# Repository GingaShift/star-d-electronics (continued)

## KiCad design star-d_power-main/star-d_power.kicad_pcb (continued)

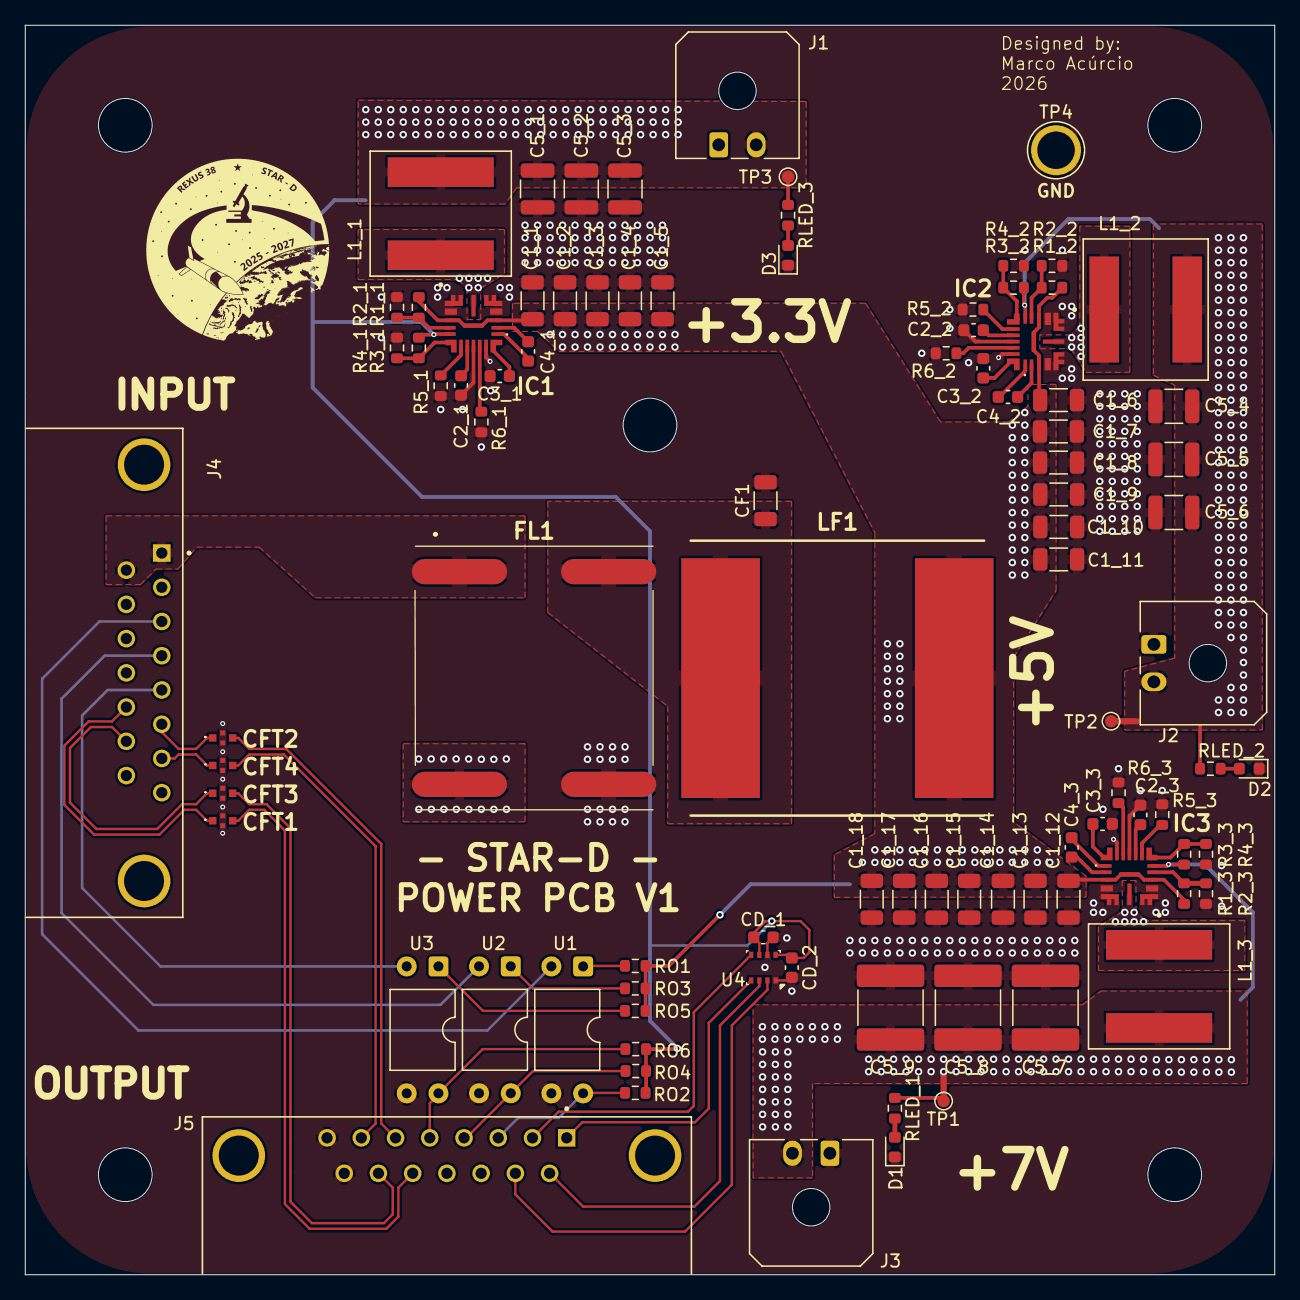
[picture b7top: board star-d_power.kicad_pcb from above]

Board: 4 copper layers, 100.0 x 100.0 mm, 94 parts (0 on the bottom side), 59 nets.

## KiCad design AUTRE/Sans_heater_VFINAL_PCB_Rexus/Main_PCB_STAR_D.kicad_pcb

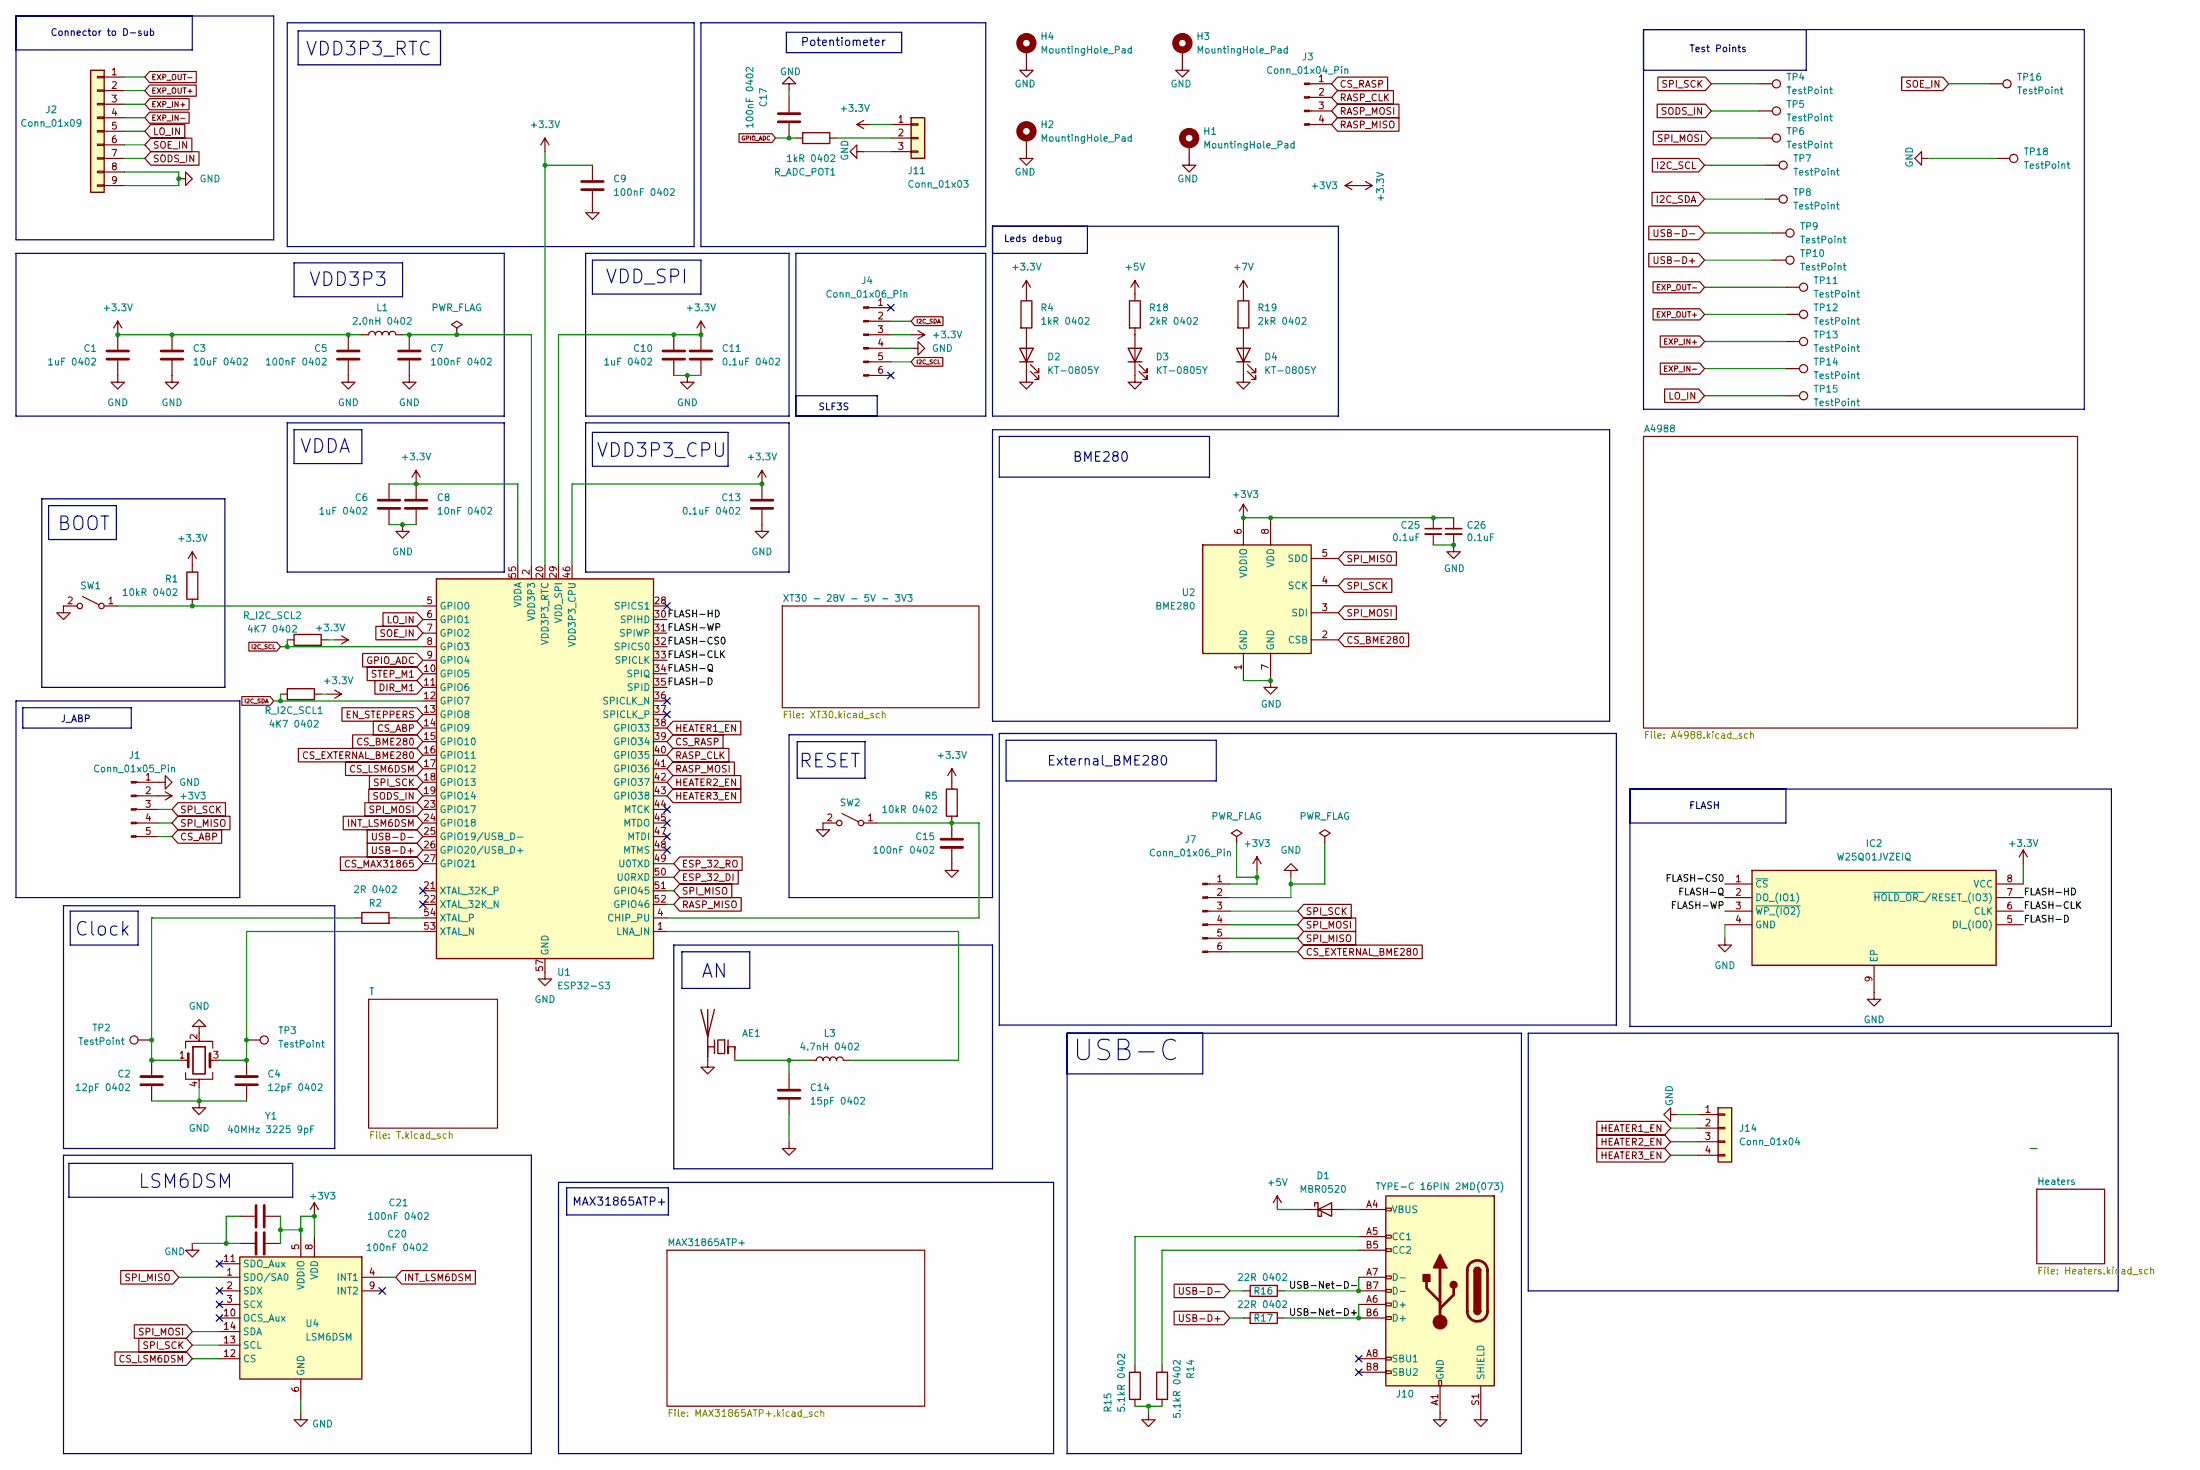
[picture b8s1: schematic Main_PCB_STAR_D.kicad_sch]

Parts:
AE1: Antenna_Chip; U.FL_Molex_MCRF_73412-0110_Vertical
C1, C6, C10: 1uF 0402; C_0402_1005Metric
C2, C4: 12pF 0402; C_0402_1005Metric
C3: 10uF 0402; C_0402_1005Metric
C5, C7, C9, C15, C17, C20, C21: 100nF 0402; C_0402_1005Metric
C8: 10nF 0402; C_0402_1005Metric
C11, C13: 0.1uF 0402; C_0402_1005Metric
C14: 15pF 0402; C_0402_1005Metric
C25, C26: 0.1uF; C_0402_1005Metric
D1: MBR0520; D_SOD-123
D2, D3, D4: KT-0805Y; LED_0805_2012Metric
H1, H2, H3, H4: MountingHole_Pad; MountingHole_4.3mm_M4_DIN965_Pad
IC2: W25Q01JVZEIQ; WSON-8-1EP_6x5mm_P1.27mm_EP3.4x4.3mm; Manufacturer_Part_Number W25Q01JVZEIQ; Mouser Part Number 454-W25Q01JVZEIQ
J1: Conn_01x05_Pin; JST_EH_S5B-EH_1x05_P2.50mm_Horizontal
J2: Conn_01x09; JST_GH_BM09B-GHS-TBT_1x09-1MP_P1.25mm_Vertical
J3: Conn_01x04_Pin; JST_EH_S4B-EH_1x04_P2.50mm_Horizontal
J4, J7: Conn_01x06_Pin; JST_EH_S6B-EH_1x06_P2.50mm_Horizontal
J10: TYPE-C 16PIN 2MD(073); USB_C_Receptacle_GCT_USB4105-xx-A_16P_TopMnt_Horizontal
J11: Conn_01x03; JST_EH_S3B-EH_1x03_P2.50mm_Horizontal
J14: Conn_01x04; JST_PH_S4B-PH-K_1x04_P2.00mm_Horizontal
L1: 2.0nH 0402; L_0402_1005Metric
L3: 4.7nH 0402; L_0402_1005Metric
R1, R5: 10kR 0402; R_0402_1005Metric
R2: 2R 0402; R_0402_1005Metric
R4: 1kR 0402; R_0402_1005Metric
R14, R15: 5.1kR 0402; R_0402_1005Metric
R16, R17: 22R 0402; R_0402_1005Metric
R18, R19: 2kR 0402; R_0402_1005Metric
R_ADC_POT1: 1kR 0402; R_0402_1005Metric
R_I2C_SCL1, R_I2C_SCL2: 4K7 0402; R_0402_1005Metric
SW1, SW2: SW_SPST; SW_Tactile_SPST_NO_Straight_CK_PTS636Sx25SMTRLFS
TP2, TP3, TP4, TP5, TP6, TP7, TP8, TP9, TP10, TP11, TP12, TP13, TP14, TP15, TP16, TP18: TestPoint; TestPoint_Pad_1.0x1.0mm
U1: ESP32-S3; QFN-56-1EP_7x7mm_P0.4mm_EP4x4mm
U2: BME280; Bosch_LGA-8_2.5x2.5mm_P0.65mm_ClockwisePinNumbering
U4: LSM6DSM; LGA-14_3x2.5mm_P0.5mm_LayoutBorder3x4y
Y1: 40MHz 3225 9pF; Crystal_SMD_3225-4Pin_3.2x2.5mm

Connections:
+3.3V: C1.1, C3.1, C5.2, C6.1, C8.1, C9.1, C10.1, C11.1, C13.1, C20.2, C21.2, C25.1, C26.1, IC2.8 (VCC), J1.2, J4.3, J7.1, J11.1, L1.1, R1.1, R4.1, R5.1, R_I2C_SCL1.2, R_I2C_SCL2.2, U1.20 (VDD3P3_RTC), U1.29 (VDD_SPI), U1.46 (VDD3P3_CPU), U1.55 (VDDA), U1.56 (VDDA), U2.6 (VDDIO), U2.8 (VDD), U4.5 (VDDIO), U4.8 (VDD); also elsewhere on the board
+5V: D1.1 (K), R18.1; also elsewhere on the board
+7V: R19.1; also elsewhere on the board
/FLASH-CLK: IC2.6 (CLK), U1.33 (SPICLK)
/FLASH-CS0: IC2.1 (~CS), U1.32 (SPICS0)
/FLASH-D: IC2.5 (DI_(IO0)), U1.35 (SPID)
/FLASH-HD: IC2.7 (~HOLD_OR_/RESET_(IO3)), U1.30 (SPIHD)
/FLASH-Q: IC2.2 (DO_(IO1)), U1.34 (SPIQ)
/FLASH-WP: IC2.3 (~WP_(IO2)), U1.31 (SPIWP)
/USB-Net-D+: J10.A6 (D+), J10.B6 (D+), R17.1
/USB-Net-D-: J10.A7 (D-), J10.B7 (D-), R16.1
CS_ABP: J1.5, U1.14 (GPIO9)
CS_BME280: U1.15 (GPIO10), U2.2 (CSB)
CS_EXTERNAL_BME280: J7.6, U1.16 (GPIO11)
CS_LSM6DSM: U1.17 (GPIO12), U4.12 (CS)
CS_MAX31865: U1.27 (GPIO21); also elsewhere on the board
CS_RASP: J3.1, U1.39 (GPIO34)
DIR_M1: U1.11 (GPIO6); also elsewhere on the board
EN_STEPPERS: U1.13 (GPIO8)
ESP_32_DI: U1.50 (U0RXD); also elsewhere on the board
ESP_32_RO: U1.49 (U0TXD); also elsewhere on the board
EXP_IN+: J2.3, TP13.1 (1_1); also elsewhere on the board
EXP_IN-: J2.4, TP14.1 (1_1); also elsewhere on the board
EXP_OUT+: J2.2, TP12.1 (1_1); also elsewhere on the board
EXP_OUT-: J2.1, TP11.1 (1_1); also elsewhere on the board
GND: AE1.2 (PCB_Trace), C1.2, C2.2, C3.2, C4.2, C5.1, C6.2, C7.1, C8.2, C9.2, C10.2, C11.2, C13.2, C14.2, C15.2, C17.2, C20.1, C21.1, C25.2, C26.2, D2.1 (K), D3.1 (K), D4.1 (K), H1.1 (1_1), H2.1 (1_1), H3.1 (1_1), H4.1 (1_1), IC2.4 (GND), IC2.9 (EP), J1.1, J2.8, J2.9, J4.4, J7.2, J10.A1 (GND), J10.A12 (GND), J10.B1 (GND), J10.B12 (GND), J10.S1 (SHIELD), J11.3, J14.1, R14.2, R15.2, SW1.2 (B), SW2.2 (B), TP18.1 (1_1), U1.57 (GND), U2.1 (GND), U2.7 (GND), U4.6 (GND), U4.7 (GND), Y1.2, Y1.4; also elsewhere on the board
GPIO_ADC: C17.1, R_ADC_POT1.2, U1.9 (GPIO4)
HEATER1_EN: J14.2, U1.38 (GPIO33)
HEATER2_EN: J14.3, U1.42 (GPIO37)
HEATER3_EN: J14.4, U1.43 (GPIO38)
I2C_SCL: J4.5, R_I2C_SCL2.1, TP7.1 (1_1), U1.8 (GPIO3)
I2C_SDA: J4.2, R_I2C_SCL1.1, TP8.1 (1_1), U1.12 (GPIO7)
INT_LSM6DSM: U1.24 (GPIO18), U4.4 (INT1)
LO_IN: J2.5, TP15.1 (1_1), U1.6 (GPIO1)
unnamed: AE1.1 (FEED), C14.1, L3.2
unnamed: C2.1, R2.1, TP2.1 (1_1), Y1.1
unnamed: C7.2, L1.2, U1.2 (VDD3P3), U1.3 (VDD3P3)
unnamed: D1.2 (A), J10.A4 (VBUS), J10.A9 (VBUS), J10.B4 (VBUS), J10.B9 (VBUS)
unnamed: D2.2 (A), R4.2
unnamed: D3.2 (A), R18.2
unnamed: D4.2 (A), R19.2
unnamed: J10.A5 (CC1), R15.1
unnamed: J10.B5 (CC2), R14.1
unnamed: J11.2, R_ADC_POT1.1
unnamed: R1.2, SW1.1 (A), U1.5 (GPIO0)
unnamed: C15.1, R5.2, SW2.1 (A), U1.4 (CHIP_PU)
unnamed: L3.1, U1.1 (LNA_IN)
unnamed: C4.1, TP3.1 (1_1), U1.53 (XTAL_N), Y1.3
unnamed: R2.2, U1.54 (XTAL_P)
RASP_CLK: J3.2, U1.40 (GPIO35)
RASP_MISO: J3.4, U1.52 (GPIO46)
RASP_MOSI: J3.3, U1.41 (GPIO36)
SODS_IN: J2.7, TP5.1 (1_1), U1.19 (GPIO14)
SOE_IN: J2.6, TP16.1 (1_1), U1.7 (GPIO2)
SPI_MISO: J1.4, J7.5, U1.51 (GPIO45), U2.5 (SDO), U4.1 (SDO/SA0); also elsewhere on the board
SPI_MOSI: J7.4, TP6.1 (1_1), U1.23 (GPIO17), U2.3 (SDI), U4.14 (SDA); also elsewhere on the board
SPI_SCK: J1.3, J7.3, TP4.1 (1_1), U1.18 (GPIO13), U2.4 (SCK), U4.13 (SCL); also elsewhere on the board
STEP_M1: U1.10 (GPIO5); also elsewhere on the board
USB-D+: R17.2, TP10.1 (1_1), U1.26 (GPIO20/USB_D+)
USB-D-: R16.2, TP9.1 (1_1), U1.25 (GPIO19/USB_D-)

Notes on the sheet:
J_ABP
VDD3P3_CPU
External_BME280
Clock
VDD3P3_RTC
BOOT
VDDA
SLF3S
RESET
BME280
FLASH
VDD3P3
Connector to D-sub
MAX31865ATP+
Leds debug
Test Points
LSM6DSM
VDD_SPI
Potentiometer
USB-C

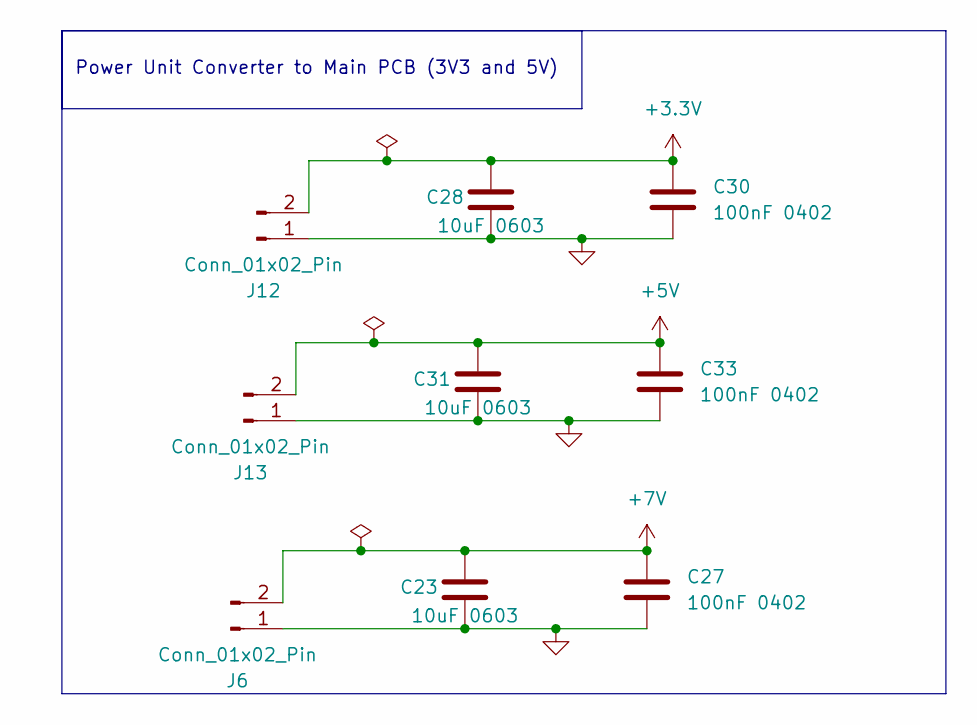
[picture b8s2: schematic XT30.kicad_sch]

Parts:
C23, C28, C31: 10uF 0603; C_0603_1608Metric
C27, C30, C33: 100nF 0402; C_0402_1005Metric
J6, J12, J13: Conn_01x02_Pin; AMASS_XT30U-F_1x02_P5.0mm_Vertical

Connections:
+3.3V: C28.1, C30.1, J12.2; also elsewhere on the board
+5V: C31.1, C33.1, J13.2; also elsewhere on the board
+7V: C23.1, C27.1, J6.2; also elsewhere on the board
GND: C23.2, C27.2, C28.2, C30.2, C31.2, C33.2, J6.1, J12.1, J13.1; also elsewhere on the board

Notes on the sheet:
Power Unit Converter to Main PCB (3V3 and 5V)

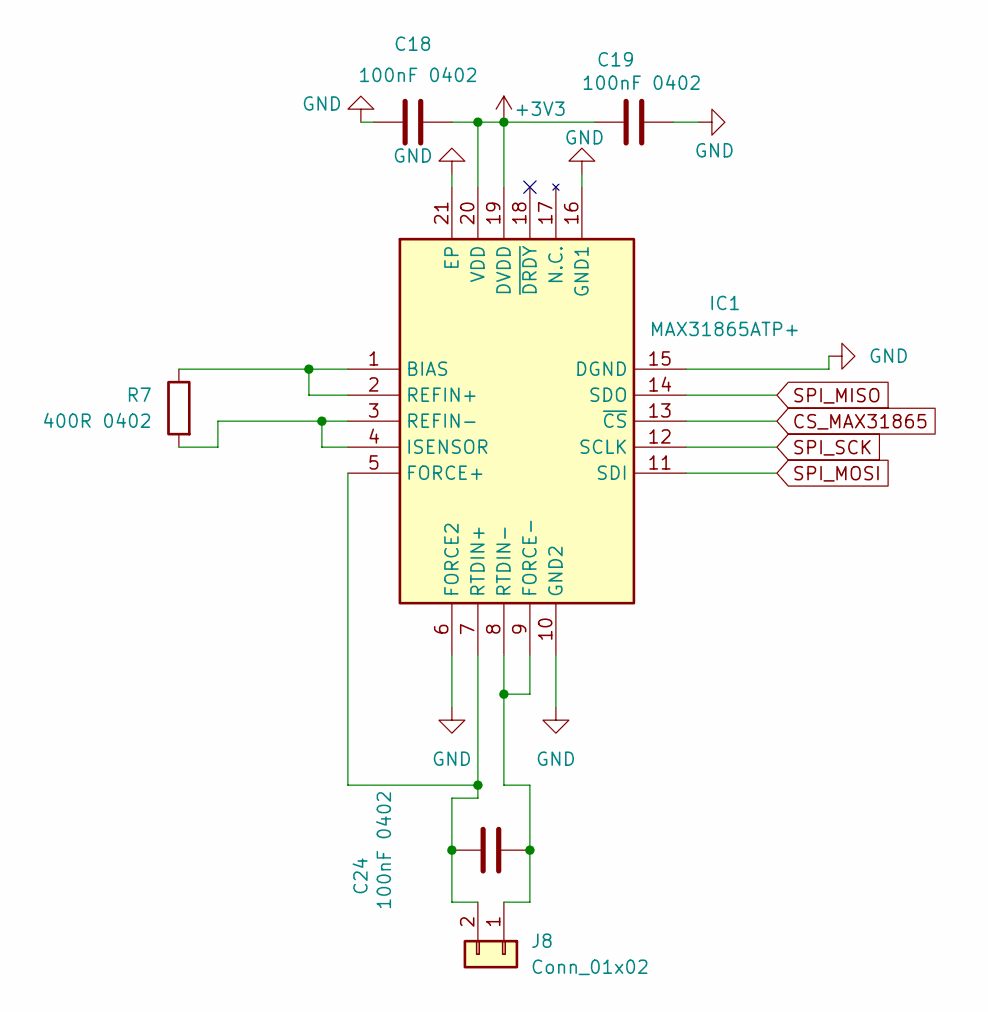
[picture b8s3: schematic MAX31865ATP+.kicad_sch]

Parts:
C18, C19, C24: 100nF 0402; C_0402_1005Metric
IC1: MAX31865ATP+; QFN65P500X500X80-21N; Manufacturer_Part_Number MAX31865ATP+; Mouser Part Number 700-MAX31865ATP+
J8: Conn_01x02; JST_EH_S2B-EH_1x02_P2.50mm_Horizontal
R7: 400R 0402; R_0402_1005Metric

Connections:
+3.3V: C18.2, C19.1, IC1.19 (DVDD), IC1.20 (VDD); also elsewhere on the board
CS_MAX31865: IC1.13 (~CS); also elsewhere on the board
GND: C18.1, C19.2, IC1.6 (FORCE2), IC1.10 (GND2), IC1.15 (DGND), IC1.16 (GND1), IC1.21 (EP); also elsewhere on the board
unnamed: IC1.1 (BIAS), IC1.2 (REFIN+), R7.1
unnamed: C24.1, IC1.5 (FORCE+), IC1.7 (RTDIN+), J8.2
unnamed: C24.2, IC1.8 (RTDIN-), IC1.9 (FORCE-), J8.1
unnamed: IC1.3 (REFIN-), IC1.4 (ISENSOR), R7.2
SPI_MISO: IC1.14 (SDO); also elsewhere on the board
SPI_MOSI: IC1.11 (SDI); also elsewhere on the board
SPI_SCK: IC1.12 (SCLK); also elsewhere on the board

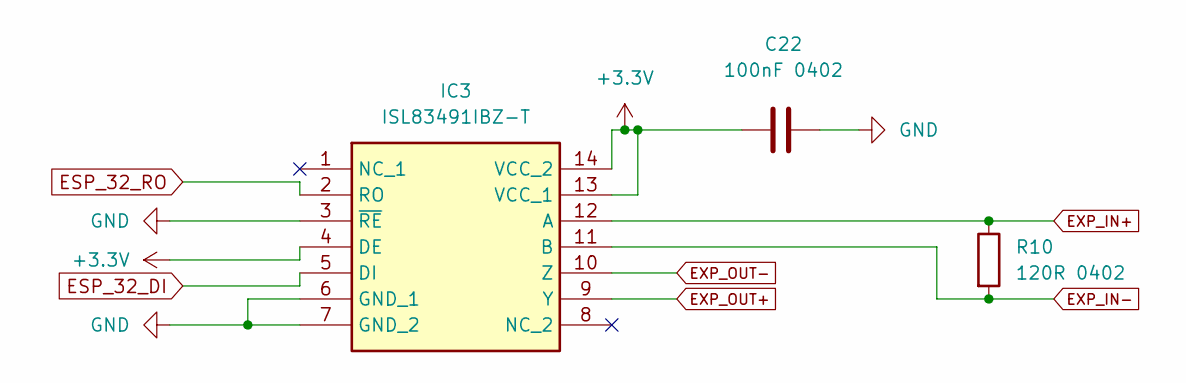
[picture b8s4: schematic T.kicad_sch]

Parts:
C22: 100nF 0402; C_0402_1005Metric
IC3: ISL83491IBZ-T; SOIC127P600X175-14N; Manufacturer_Part_Number ISL83491IBZ-T; Mouser Part Number 968-ISL83491IBZ-T
R10: 120R 0402; R_0402_1005Metric

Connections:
+3.3V: C22.1, IC3.4 (DE), IC3.13 (VCC_1), IC3.14 (VCC_2); also elsewhere on the board
ESP_32_DI: IC3.5 (DI); also elsewhere on the board
ESP_32_RO: IC3.2 (RO); also elsewhere on the board
EXP_IN+: IC3.12 (A), R10.1; also elsewhere on the board
EXP_IN-: IC3.11 (B), R10.2; also elsewhere on the board
EXP_OUT+: IC3.9 (Y); also elsewhere on the board
EXP_OUT-: IC3.10 (Z); also elsewhere on the board
GND: C22.2, IC3.3 (~RE), IC3.6 (GND_1), IC3.7 (GND_2); also elsewhere on the board

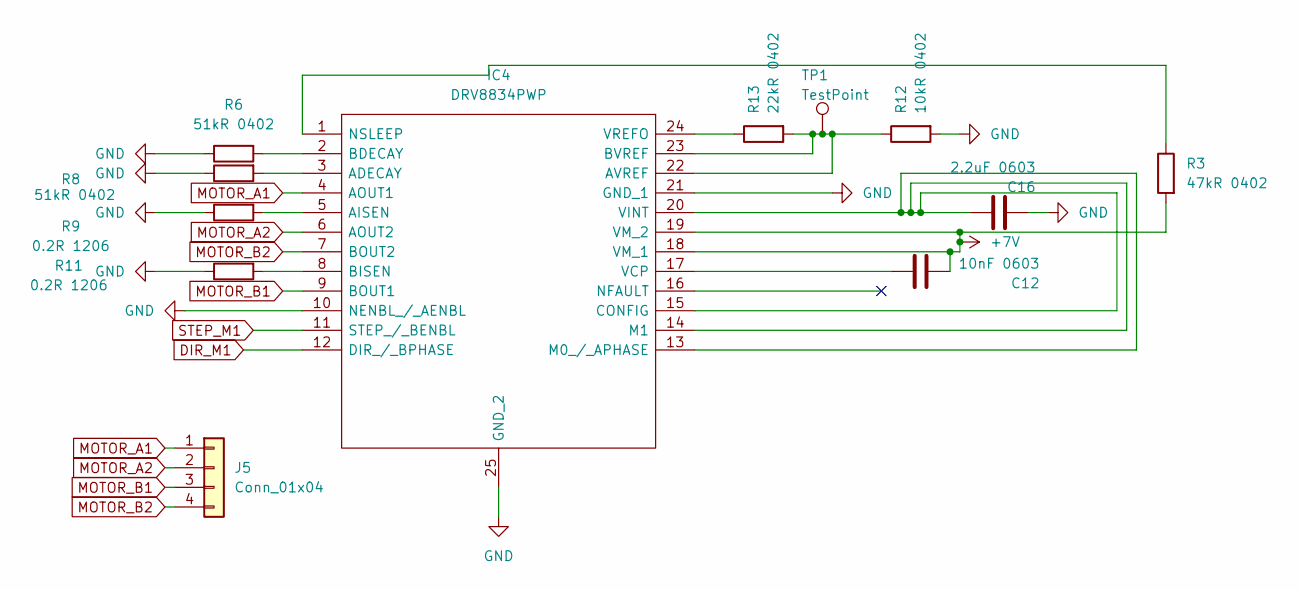
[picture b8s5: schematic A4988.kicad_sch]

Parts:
C12: 10nF 0603; C_0402_1005Metric
C16: 2.2uF 0603; C_0402_1005Metric
IC4: DRV8834PWP; SOP65P640X120-25N; Manufacturer_Part_Number DRV8834PWP; Mouser Part Number 595-DRV8834PWP
J5: Conn_01x04; JST_PH_S4B-PH-K_1x04_P2.00mm_Horizontal
R3: 47kR 0402; R_0402_1005Metric
R6, R8: 51kR 0402; R_0402_1005Metric
R9, R11: 0.2R 1206; R_0402_1005Metric
R12: 10kR 0402; R_0402_1005Metric
R13: 22kR 0402; R_0402_1005Metric
TP1: TestPoint; TestPoint_Pad_1.0x1.0mm

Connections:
+7V: C12.1, IC4.18 (VM_1), IC4.19 (VM_2), R3.2; also elsewhere on the board
DIR_M1: IC4.12 (DIR_/_BPHASE); also elsewhere on the board
GND: C16.2, IC4.10 (NENBL_/_AENBL), IC4.21 (GND_1), IC4.25 (GND_2), R6.1, R8.1, R9.1, R11.1, R12.2; also elsewhere on the board
MOTOR_A1: IC4.4 (AOUT1), J5.1
MOTOR_A2: IC4.6 (AOUT2), J5.2
MOTOR_B1: IC4.9 (BOUT1), J5.3
MOTOR_B2: IC4.7 (BOUT2), J5.4
unnamed: IC4.3 (ADECAY), R8.2
unnamed: IC4.5 (AISEN), R9.2
unnamed: IC4.22 (AVREF), IC4.23 (BVREF), R12.1, R13.2, TP1.1 (1_1)
unnamed: IC4.2 (BDECAY), R6.2
unnamed: IC4.8 (BISEN), R11.2
unnamed: C16.1, IC4.13 (M0_/_APHASE), IC4.14 (M1), IC4.15 (CONFIG), IC4.20 (VINT)
unnamed: IC4.1 (NSLEEP), R3.1
unnamed: C12.2, IC4.17 (VCP)
unnamed: IC4.24 (VREFO), R13.1
STEP_M1: IC4.11 (STEP_/_BENBL); also elsewhere on the board

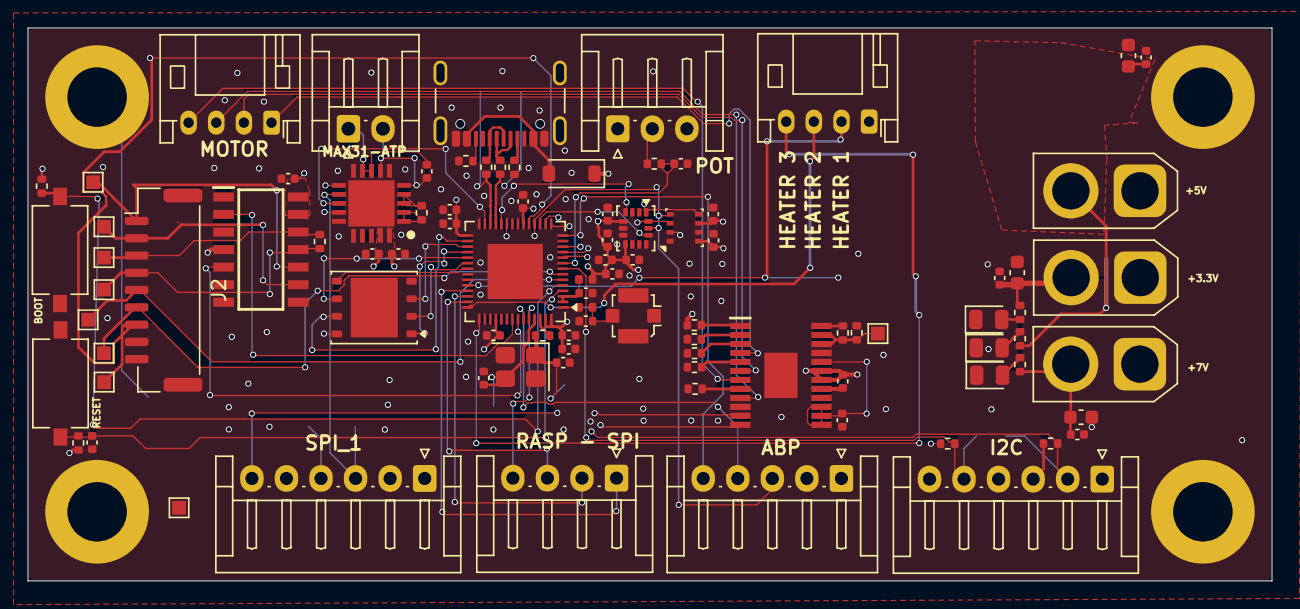
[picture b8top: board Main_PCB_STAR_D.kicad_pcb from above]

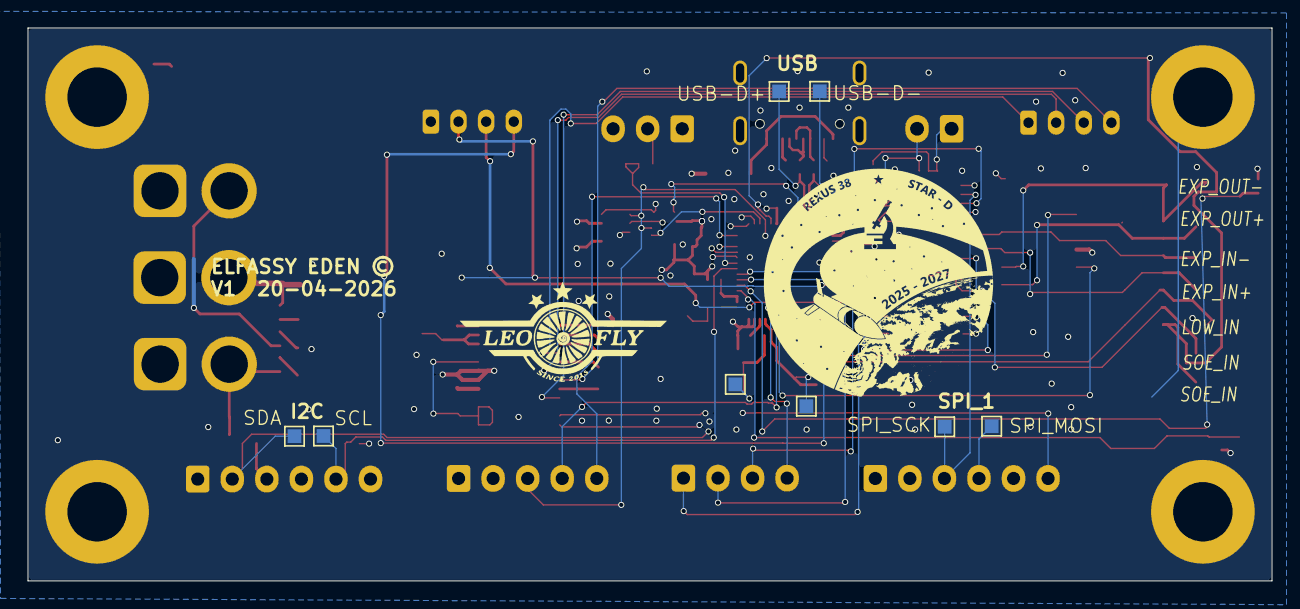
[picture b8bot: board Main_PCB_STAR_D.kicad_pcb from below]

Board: 4 copper layers, 90.0 x 40.0 mm, 104 parts (8 on the bottom side), 76 nets.

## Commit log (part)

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2026-02-16 Initial STAR-D control PCB upload
2026-05-30 Create Main_Board
